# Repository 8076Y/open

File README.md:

# open
Design files for our Robocup Junior Soccer Open robots

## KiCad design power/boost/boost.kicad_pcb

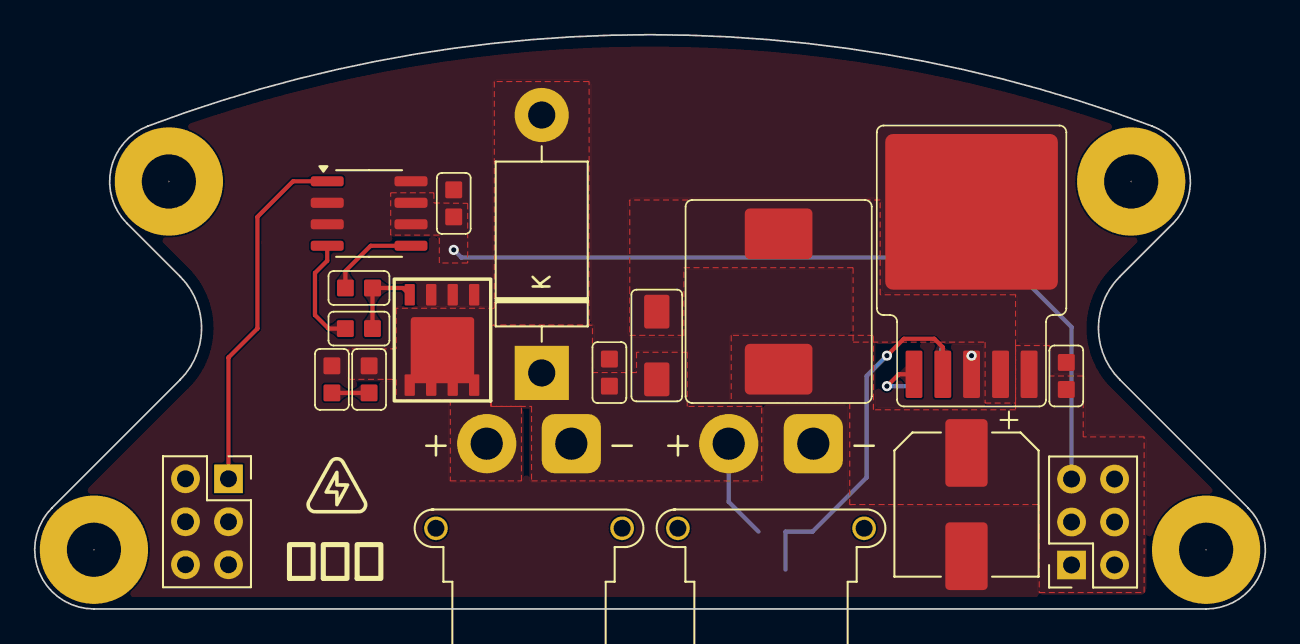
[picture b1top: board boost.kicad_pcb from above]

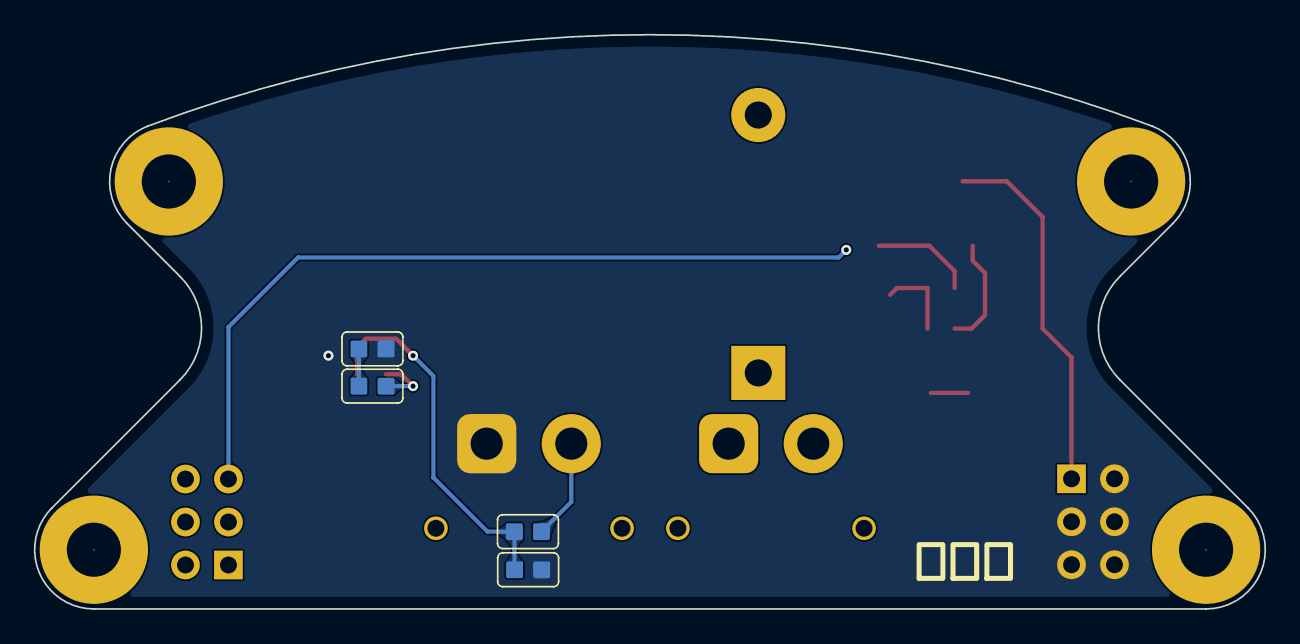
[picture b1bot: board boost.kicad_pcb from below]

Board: 2 copper layers, 72.7 x 33.9 mm, 26 parts (4 on the bottom side), 13 nets.

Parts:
BC1, BC3: 0u1; cap0603
BC2: 100u; CP_Elec_8x6.5
BC4: 1u; cap0603
BD1: SS510; SMA (DO-214AC)
BIC1: LM2587S-ADJ; TO170P1435X465-6N
BJ1: XT30; AMASS_XT30PW-F_1x02_P2.50mm_Horizontal
BL1: 68uH; 1040 One Piece Inductor
BR1: 57K; res0603
BR2: 2k94; res0603
BR3: 1K5; res0603
BSC1: 0.1u; res0603
BSC2: 1n5; cap0603
BSD1: 1N5401; D_DO-201AD_P15.24mm_Horizontal
BSJ1: XT30; AMASS_XT30PW-F_1x02_P2.50mm_Horizontal
BSQ1: ISC011N06LM5ATMA1; 8-DFN (5x6)
BSR1: 20R; res0603
BSR2, BSR3: 100; res0603
BSU1: NCP81074AMNTBG; SOIC-8_3.9x4.9mm_P1.27mm
H1, H2, H3, H4: MountingHole; MountingHole_3.2mm_M3_Pad
J1, J2: Conn_02x03_Counter_Clockwise; PinSocket_2x03_P2.54mm_Vertical

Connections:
+12V: BC1.1, BC2.1, BIC1.5 (VIN), BL1.1, BSC1.1, BSU1.6 (VDD), BSU1.7 (VDD), J1.1, J1.2, J1.3, J1.4, J1.5, J1.6
+48V: BC3.1, BD1.1 (K), BJ1.2, BR1.1, BSD1.1 (K), BSJ1.1
/Sol: BSU1.1 (IN+), J2.1
GND: BC1.2, BC2.2, BC3.2, BC4.2, BIC1.3 (GND), BIC1.6 (TAB), BJ1.1, BR3.2, BSC1.2, BSC2.2, BSQ1.1 (S), BSQ1.2 (S), BSQ1.3 (S), BSU1.2 (GND), BSU1.3 (GND), BSU1.8 (IN-), J2.2, J2.3, J2.4, J2.5, J2.6
unnamed: BC4.1, BR2.2
unnamed: BD1.2 (A), BIC1.4 (SW), BL1.2
unnamed: BIC1.1 (COMP), BR2.1
unnamed: BIC1.2 (FDBK), BR1.2, BR3.1
unnamed: BSC2.1, BSR1.2
unnamed: BSD1.2 (A), BSJ1.2, BSQ1.5 (D), BSQ1.6 (D), BSQ1.7 (D), BSQ1.8 (D), BSQ1.9 (D), BSR1.1
unnamed: BSQ1.4 (G), BSR2.2, BSR3.2
unnamed: BSR2.1, BSU1.5 (OUTH)
unnamed: BSR3.1, BSU1.4 (OUTL)

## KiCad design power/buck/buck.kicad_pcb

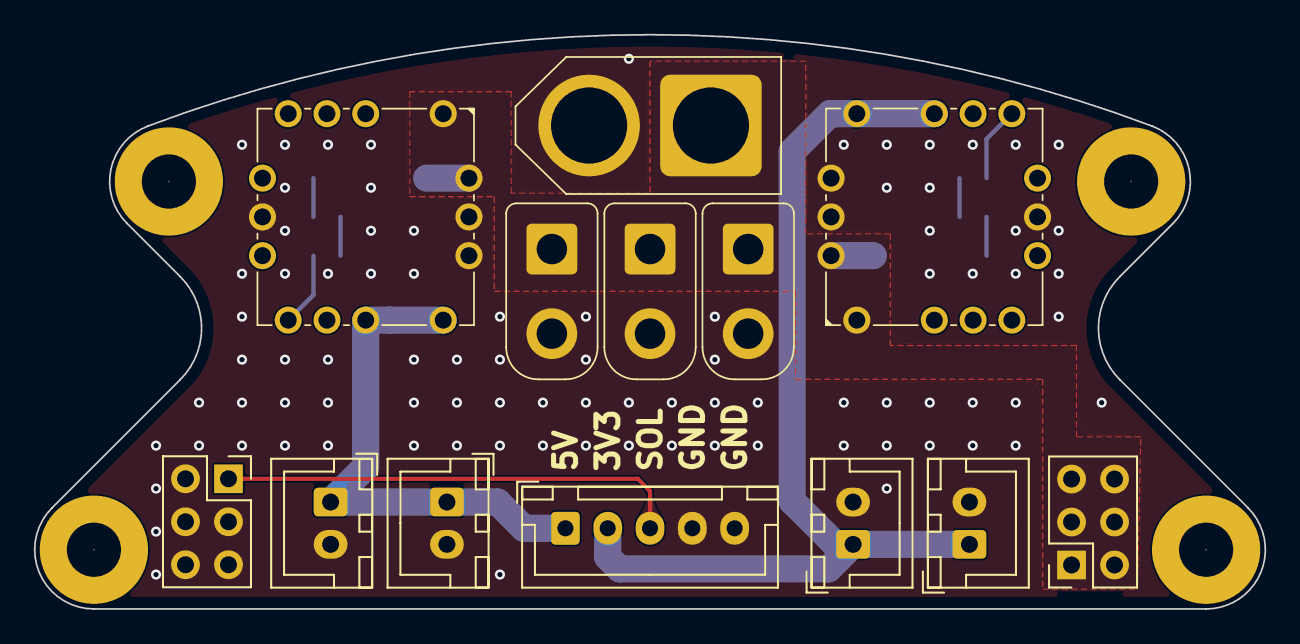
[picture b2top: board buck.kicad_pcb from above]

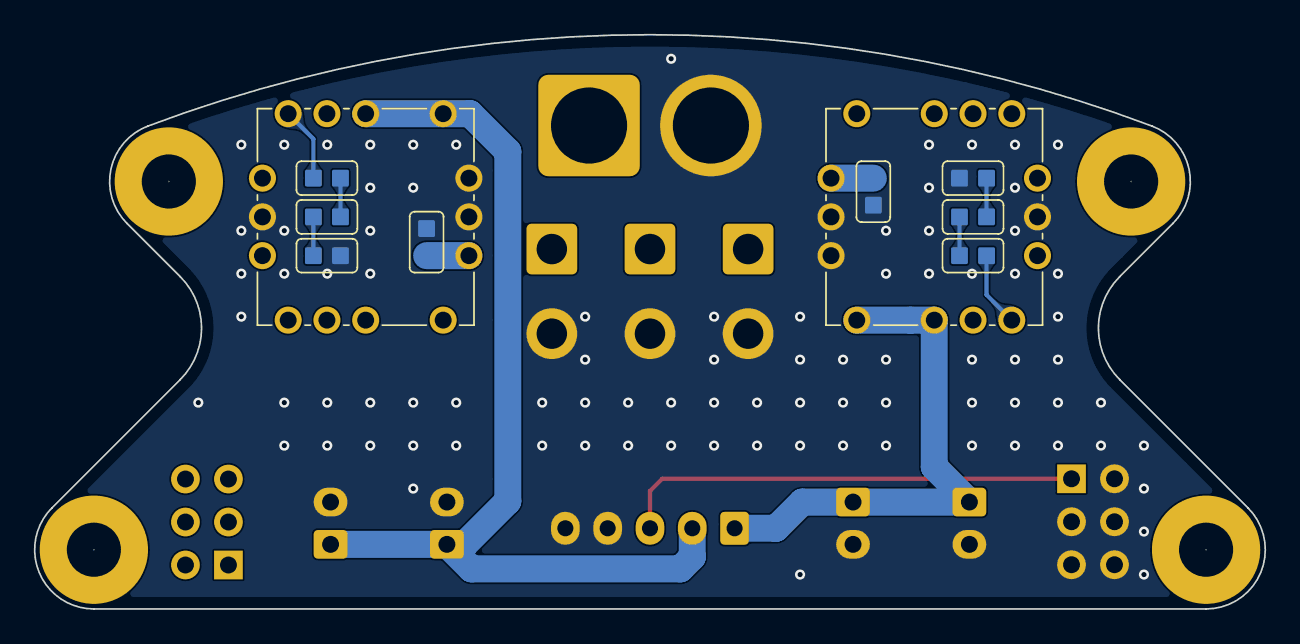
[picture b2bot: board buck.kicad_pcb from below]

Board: 2 copper layers, 72.7 x 33.9 mm, 25 parts (8 on the bottom side), 11 nets.

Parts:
C1, C2: 10u; cap0603
H1, H2, H3, H4: MountingHole; MountingHole_3.2mm_M3_Pad
J1: 12V; PinSocket_2x03_P2.54mm_Vertical
J2: GND; PinSocket_2x03_P2.54mm_Vertical
J3: VBAT; xt60-f
J4: Motor; xt30-f
J5: Drib A; xt30-f
J6: Drib B; xt30-f
J7, J9: L1; JST_XH_B2B-XH-A_1x02_P2.50mm_Vertical
J8, J10: SPARE; JST_XH_B2B-XH-A_1x02_P2.50mm_Vertical
J11: Conn_01x05; JST_XH_B5B-XH-A_1x05_P2.50mm_Vertical
R1, R2, R3: 1K; res0603
R4: 330; res0603
R5: 180; res0603
R6: 10; res0603
U1, U2: OKL-T6-W12P-C; MURATA_OKL-T-6-W12

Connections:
+3V3: J7.1, J8.1, J11.1, U1.4 (OUT), U1.5 (SENSE)
+5V: J9.1, J10.1, J11.2, U2.4 (OUT), U2.5 (SENSE)
+12V: C1.1, C2.1, J1.1, J1.2, J1.3, J1.4, J1.5, J1.6, J3.1, J4.1, J5.1, J6.1, U1.2 (VIN), U2.2 (VIN)
/KICK SIG: J2.1, J11.3
GND: C1.2, C2.2, J2.2, J2.3, J2.4, J2.5, J2.6, J3.2, J4.2, J5.2, J6.2, J7.2, J8.2, J9.2, J10.2, J11.4, J11.5, R5.2, R6.2, U1.3 (GND), U1.7 (GND), U2.3 (GND), U2.7 (GND)
unnamed: R1.2, R3.1
unnamed: R2.2, R4.1
unnamed: R3.2, R5.1
unnamed: R4.2, R6.1
unnamed: R1.1, U1.6 (TRIM)
unnamed: R2.1, U2.6 (TRIM)

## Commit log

2026-05-19 chore: init
2026-05-19 feat: kicad libraries
2026-05-19 feat: power supply units
2026-05-19 chore: add gitignore
2026-05-19 chore: remove gitignored files
2026-05-19 chore: change license
2026-05-19 chore: license
